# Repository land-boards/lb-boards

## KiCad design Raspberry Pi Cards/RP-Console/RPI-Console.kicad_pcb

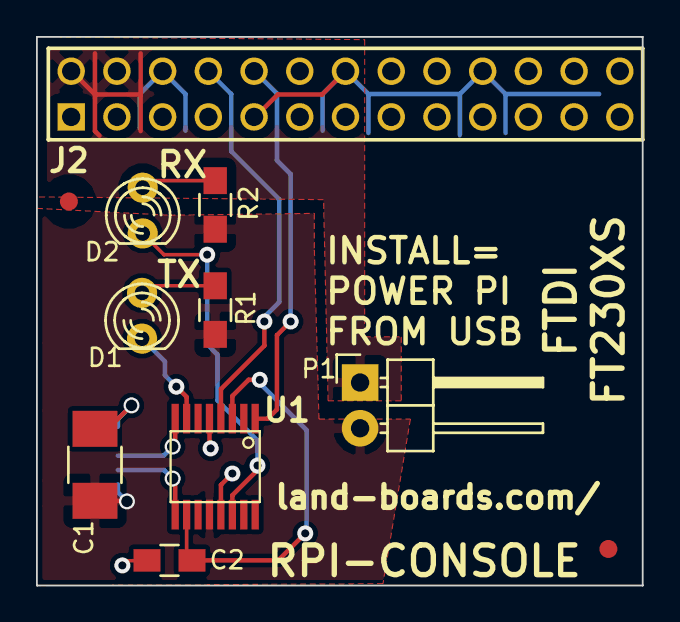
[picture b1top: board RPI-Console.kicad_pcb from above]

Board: 2 copper layers, 33.7 x 30.5 mm, 12 parts (1 on the bottom side), 12 nets.

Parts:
C1: 10uF; C_1210_HandSoldering
C2: 0.1uF; C_0805_HandSoldering
D1, D2: LED; LED-3MM
FID1, FID2: CONN_1; FIDUCIAL
J1: USB-B; USB-B-MINI
J2: RASPIO; pin_array_13x2
P1: CONN_2; Pin_Header_Angled_1x02
R1, R2: 270; R_0805_HandSoldering
U1: FT230XS; ssop-16

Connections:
/+3.3V-USB: C2.1, U1.3, U1.10
/+5V: J2.2, J2.4, P1.1
/+5V-USB: C1.1, J1.1, P1.2, R1.1, R2.1, U1.12
/DM: J1.2, U1.9
/DP: J1.3, U1.8
/GND: C1.2, C2.2, J1.4, J2.6, J2.9, J2.14, J2.20, J2.25, U1.5, U1.13
/PI2USB: J2.8, U1.4
/PUP0: D1.1, R1.2
/PUP1: D2.1, R2.2
/RXLED*: D2.2, U1.14
/TXLED*: D1.2, U1.7
/USB2PI: J2.10, U1.1

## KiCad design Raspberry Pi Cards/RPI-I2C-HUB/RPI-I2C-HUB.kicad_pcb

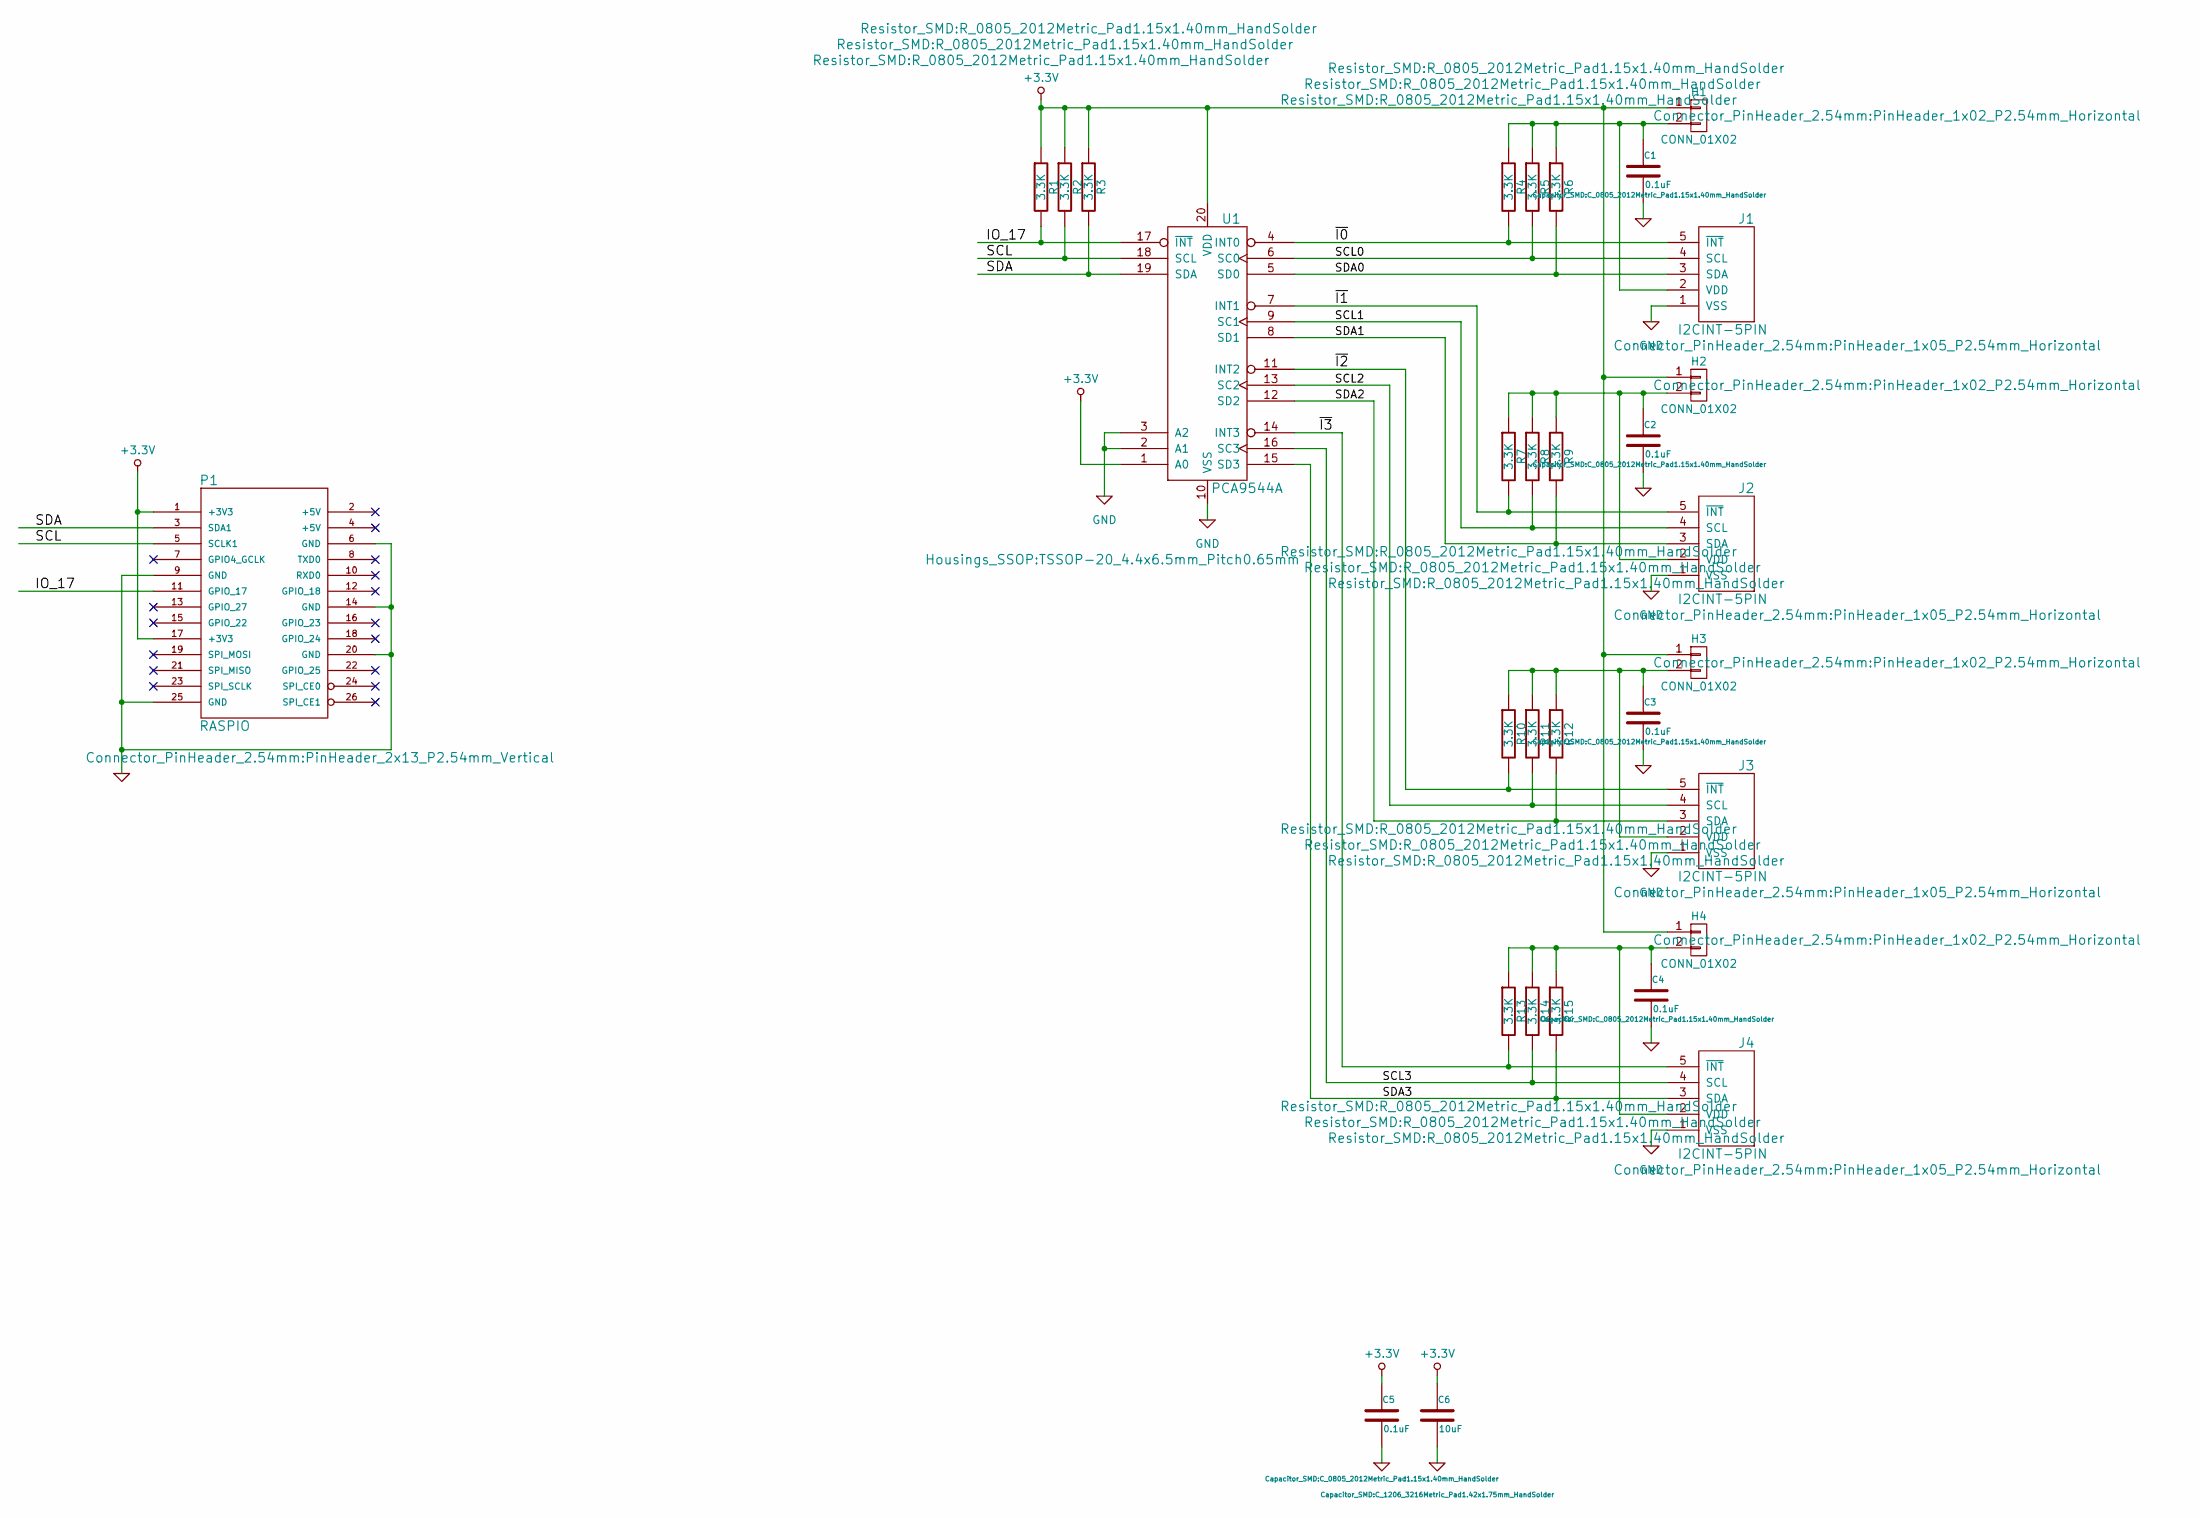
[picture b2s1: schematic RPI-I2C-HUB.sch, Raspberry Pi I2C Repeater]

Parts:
C1, C2, C3, C4, C5: 0.1uF; C_0805_2012Metric_Pad1.15x1.40mm_HandSolder
C6: 10uF; C_1206_3216Metric_Pad1.42x1.75mm_HandSolder
H1, H2, H3, H4: CONN_01X02; PinHeader_1x02_P2.54mm_Horizontal
J1, J2, J3, J4: I2CINT-5PIN; PinHeader_1x05_P2.54mm_Horizontal
P1: RASPIO; PinHeader_2x13_P2.54mm_Vertical
R1, R2, R3, R4, R5, R6, R7, R8, R9, R10, R11, R12, R13, R14, R15: 3.3K; R_0805_2012Metric_Pad1.15x1.40mm_HandSolder
U1: PCA9544A; TSSOP-20_4.4x6.5mm_Pitch0.65mm

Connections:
+3.3V: C5.1, C6.1, H1.1, H2.1, H3.1, H4.1, P1.1 (+3V3), P1.17 (+3V3), R1.1, R2.1, R3.1, U1.1 (A0), U1.20 (VDD)
/IO_17: P1.11 (GPIO_17), R1.2, U1.17 (~INT)
/SCL: P1.5 (SCLK1), R2.2, U1.18 (SCL)
/SCL0: J1.4 (SCL), R5.2, U1.6 (SC0)
/SCL1: J2.4 (SCL), R8.2, U1.9 (SC1)
/SCL2: J3.4 (SCL), R11.2, U1.13 (SC2)
/SCL3: J4.4 (SCL), R14.2, U1.16 (SC3)
/SDA: P1.3 (SDA1), R3.2, U1.19 (SDA)
/SDA0: J1.3 (SDA), R6.2, U1.5 (SD0)
/SDA1: J2.3 (SDA), R9.2, U1.8 (SD1)
/SDA2: J3.3 (SDA), R12.2, U1.12 (SD2)
/SDA3: J4.3 (SDA), R15.2, U1.15 (SD3)
/~I0: J1.5 (~INT), R4.2, U1.4 (INT0)
/~I1: J2.5 (~INT), R7.2, U1.7 (INT1)
/~I2: J3.5 (~INT), R10.2, U1.11 (INT2)
/~I3: J4.5 (~INT), R13.2, U1.14 (INT3)
GND: C1.2, C2.2, C3.2, C4.2, C5.2, C6.2, J1.1 (VSS), J2.1 (VSS), J3.1 (VSS), J4.1 (VSS), P1.6 (GND), P1.9 (GND), P1.14 (GND), P1.20 (GND), P1.25 (GND), U1.2 (A1), U1.3 (A2), U1.10 (VSS)
unnamed: C1.1, H1.2, J1.2 (VDD), R4.1, R5.1, R6.1
unnamed: C2.1, H2.2, J2.2 (VDD), R7.1, R8.1, R9.1
unnamed: C3.1, H3.2, J3.2 (VDD), R10.1, R11.1, R12.1
unnamed: C4.1, H4.2, J4.2 (VDD), R13.1, R14.1, R15.1

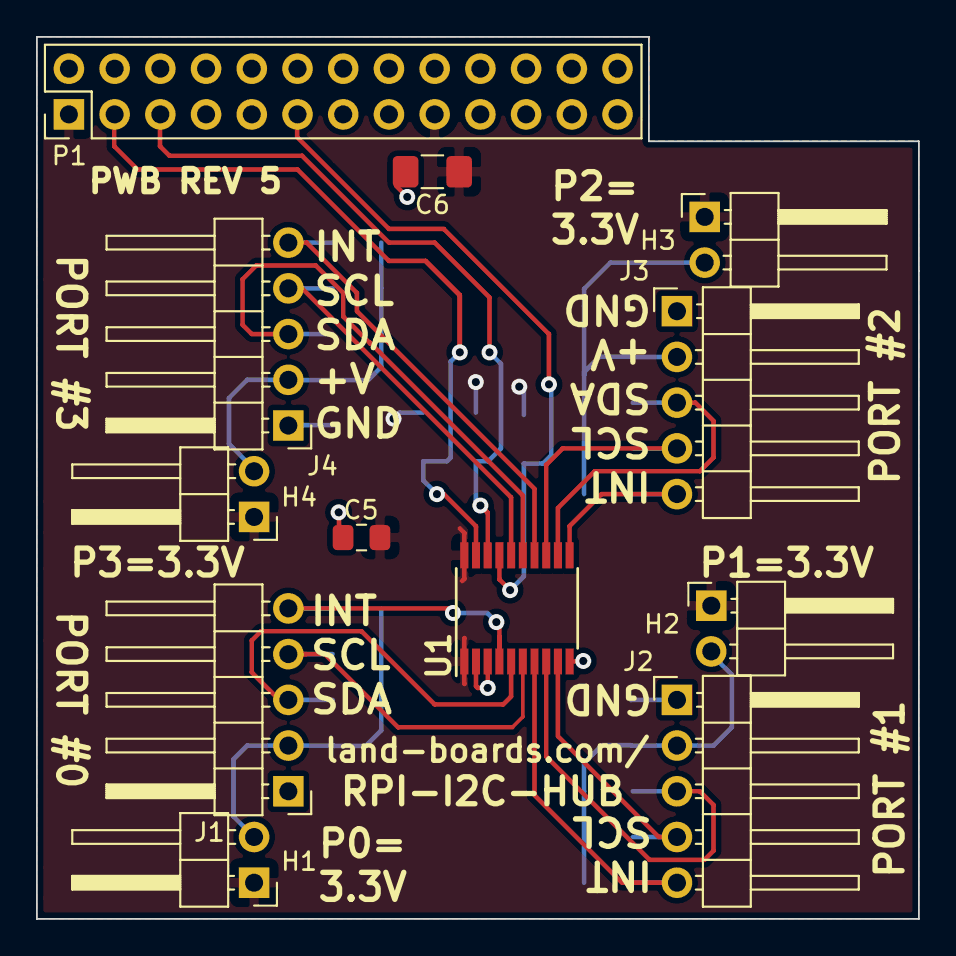
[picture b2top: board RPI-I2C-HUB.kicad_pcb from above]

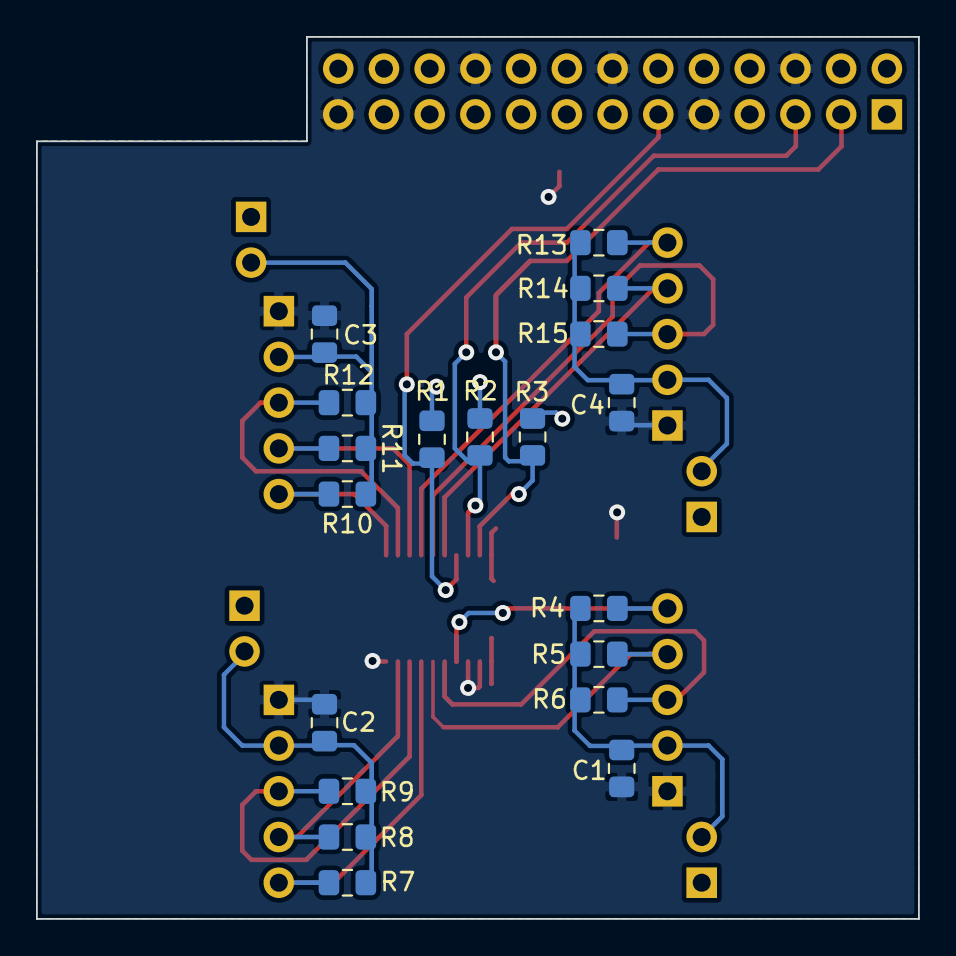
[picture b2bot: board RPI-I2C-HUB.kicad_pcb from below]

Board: 2 copper layers, 49.0 x 49.0 mm, 31 parts (19 on the bottom side), 21 nets.

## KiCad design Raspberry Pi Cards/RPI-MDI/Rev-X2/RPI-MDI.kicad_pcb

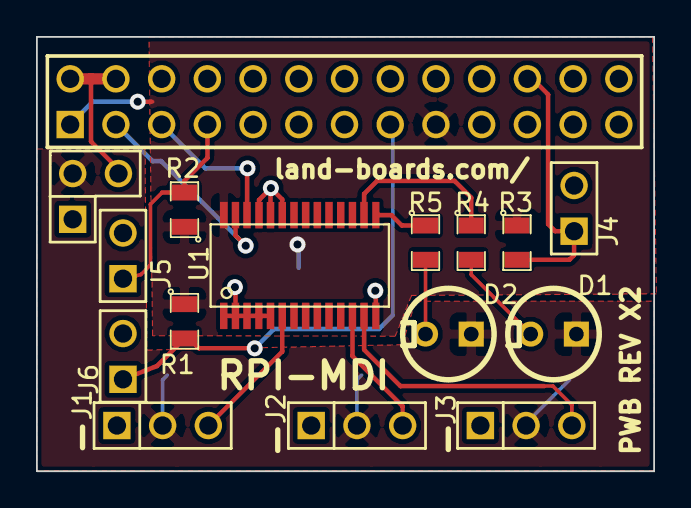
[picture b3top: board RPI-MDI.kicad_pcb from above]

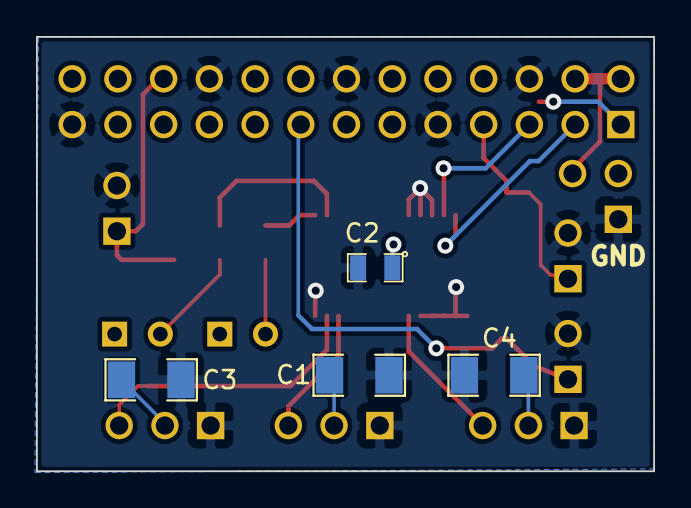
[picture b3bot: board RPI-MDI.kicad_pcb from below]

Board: 2 copper layers, 34.3 x 24.1 mm, 20 parts (4 on the bottom side), 16 nets.

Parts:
C1, C3, C4: 106; SM1206
C2: 104; SM0805
D1, D2: LED; LEDV
J1, J2, J3: CONN_3; PIN_ARRAY_3X1
J4, J5, J6: CONN_2; PIN_ARRAY_2X1
J8: CONN_3; PIN_ARRAY_3P_L
P1: RASPIO; pin_array_13x2
R1, R2, R3: 3.9K; SM0805
R4, R5: 120; SM0805
U1: PCA9685; tssop-28

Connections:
/+3.3V: C2.1, P1.1, P1.17, R1.1, R2.1, R3.1, U1.28
/IO_4: J5.1, P1.7, R2.2
/IO_22: J6.1, P1.15, R1.2
/IO_25: J4.1, P1.22, R3.2
/R5: C1.1, C3.1, C4.1, D1.1, D2.1, J1.2, J2.2, J3.2, J8.2
/SCLK1: P1.5, U1.26
/SDA1: P1.3, U1.27
GND: C1.2, C2.2, C3.2, C4.2, J1.1, J2.1, J3.1, J4.2, J5.2, J6.2, J8.1, P1.6, P1.9, P1.14, P1.20, P1.25, U1.1, U1.2, U1.3, U1.4, U1.5, U1.14, U1.23, U1.24, U1.25
unnamed: J1.3, U1.6
unnamed: J3.3, U1.13
unnamed: J2.3, U1.12
unnamed: R4.1, U1.16
unnamed: R5.1, U1.15
unnamed: D1.2, R4.2
unnamed: D2.2, R5.2
unnamed: J8.3, P1.2, P1.4

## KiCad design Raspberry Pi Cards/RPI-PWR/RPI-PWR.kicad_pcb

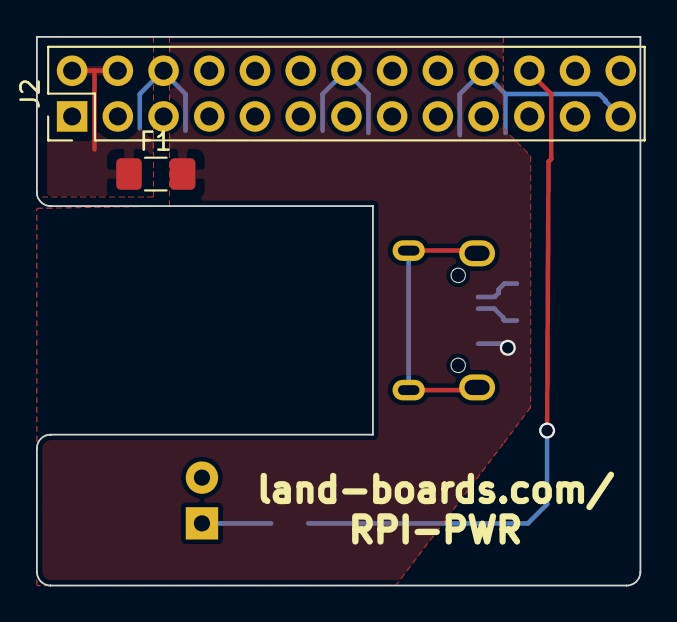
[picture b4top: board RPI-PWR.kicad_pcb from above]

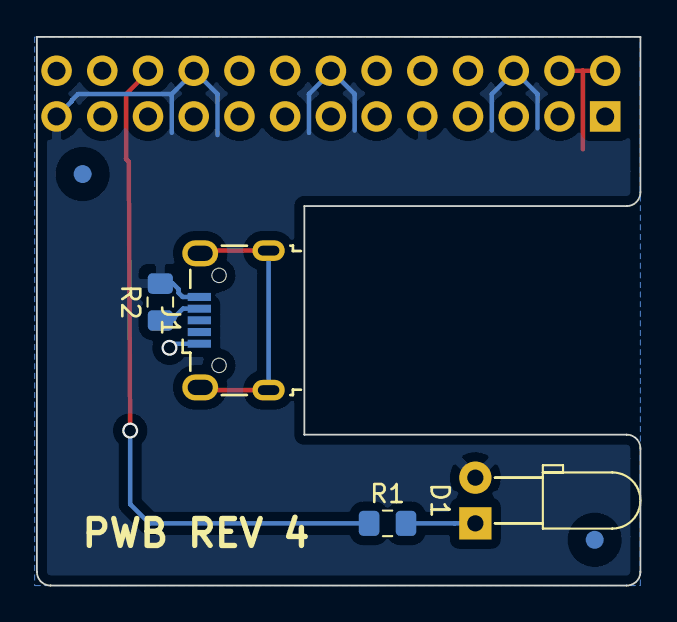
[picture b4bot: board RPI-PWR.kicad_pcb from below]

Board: 2 copper layers, 33.5 x 30.5 mm, 8 parts (6 on the bottom side), 6 nets.

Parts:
D1: LED; LED_D3.0mm_Horizontal_O3.81mm_Z2.0mm
F1: FUSE; R_1206_3216Metric_Pad1.42x1.75mm_HandSolder
FID1, FID2: CONN_1; FIDUCIAL
J1: USB-MICRO-B; USB_Micro-B_Wuerth_629105150521
J2: CONN, FEM, 2X13; PinHeader_2x13_P2.54mm_Vertical
R1: 270; R_0805_2012Metric_Pad1.15x1.40mm_HandSolder
R2: 130K; R_0805_2012Metric_Pad1.15x1.40mm_HandSolder

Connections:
/+5V: F1.1, J2.2, J2.4
/+5V-USB: F1.2, J1.1
/GND: D1.2, J1.5, J2.6, J2.9, J2.14, J2.20, J2.25, R2.2
/PUP0: D1.1, R1.2
unnamed: J1.4, R2.1
unnamed: J2.22, R1.1

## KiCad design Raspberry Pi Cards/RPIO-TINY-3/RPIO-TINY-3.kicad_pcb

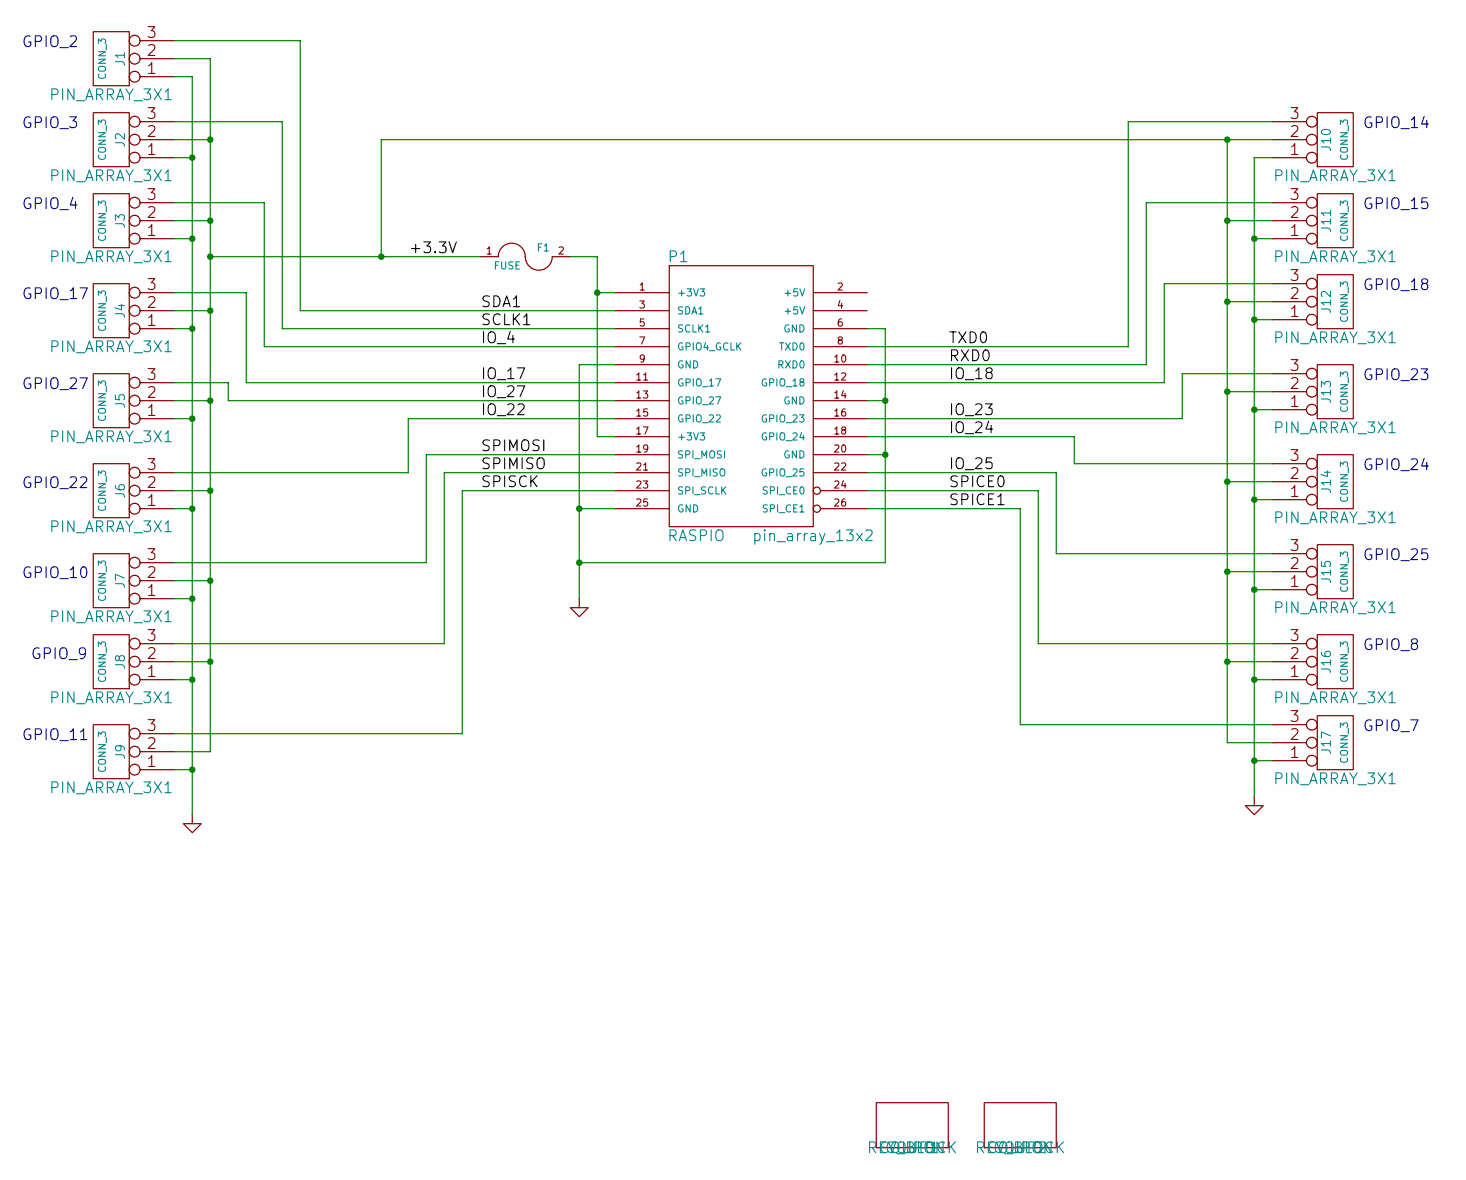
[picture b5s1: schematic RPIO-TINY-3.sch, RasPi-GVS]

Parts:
COUP1, COUP2: COUPON; REV_BLOCK
F1: FUSE
J1, J2, J3, J4, J5, J6, J7, J8, J9, J10, J11, J12, J13, J14, J15, J16, J17: CONN_3; PIN_ARRAY_3X1
P1: RASPIO; pin_array_13x2

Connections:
/+3.3V: F1.1, J1.2 (PM), J2.2 (PM), J3.2 (PM), J4.2 (PM), J5.2 (PM), J6.2 (PM), J7.2 (PM), J8.2 (PM), J9.2 (PM), J10.2 (PM), J11.2 (PM), J12.2 (PM), J13.2 (PM), J14.2 (PM), J15.2 (PM), J16.2 (PM), J17.2 (PM)
/IO_4: J3.3, P1.7 (GPIO4_GCLK)
/IO_17: J4.3, P1.11 (GPIO_17)
/IO_18: J12.3, P1.12 (GPIO_18)
/IO_22: J6.3, P1.15 (GPIO_22)
/IO_23: J13.3, P1.16 (GPIO_23)
/IO_24: J14.3, P1.18 (GPIO_24)
/IO_25: J15.3, P1.22 (GPIO_25)
/IO_27: J5.3, P1.13 (GPIO_27)
/RXD0: J11.3, P1.10 (RXD0)
/SCLK1: J2.3, P1.5 (SCLK1)
/SDA1: J1.3, P1.3 (SDA1)
/SPICE0: J16.3, P1.24 (SPI_CE0)
/SPICE1: J17.3, P1.26 (SPI_CE1)
/SPIMISO: J8.3, P1.21 (SPI_MISO)
/SPIMOSI: J7.3, P1.19 (SPI_MOSI)
/SPISCK: J9.3, P1.23 (SPI_SCLK)
/TXD0: J10.3, P1.8 (TXD0)
GND: J1.1, J2.1, J3.1, J4.1, J5.1, J6.1, J7.1, J8.1, J9.1, J10.1, J11.1, J12.1, J13.1, J14.1, J15.1, J16.1, J17.1, P1.6 (GND), P1.9 (GND), P1.14 (GND), P1.20 (GND), P1.25 (GND)
unnamed: F1.2, P1.1 (+3V3), P1.17 (+3V3)

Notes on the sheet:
GPIO_2
GPIO_3
GPIO_4
GPIO_17
GPIO_27
GPIO_22
GPIO_10
GPIO_9
GPIO_11
GPIO_14
GPIO_15
GPIO_18
GPIO_23
GPIO_24
GPIO_25
GPIO_8
GPIO_7

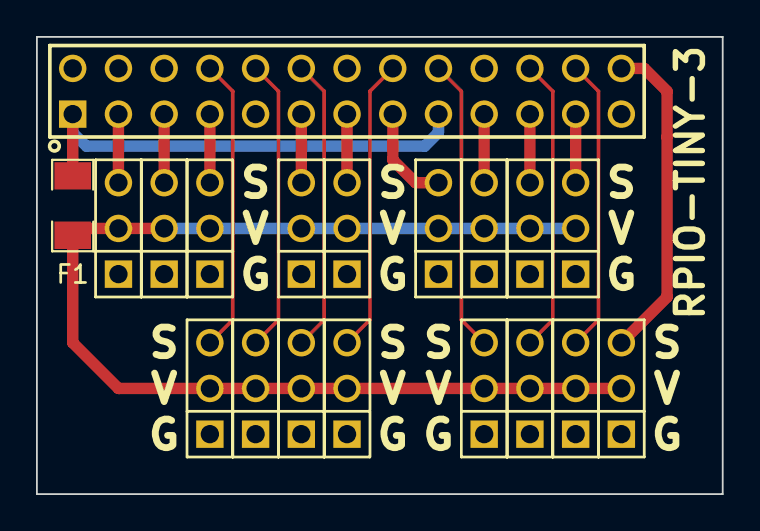
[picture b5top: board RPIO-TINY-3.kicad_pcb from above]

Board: 2 copper layers, 38.1 x 25.4 mm, 19 parts (0 on the bottom side), 20 nets.
